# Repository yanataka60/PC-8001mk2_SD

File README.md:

# PC-8001mk2にSD-CARDからCMT形式ファイルのロード、セーブ機能

　PC-8001mk2でSD-CARDからCMT形式ファイルのロード、セーブ機能を実現するものです。

#### (2023.4.24追記)PC-8001mk2SRでは、Nモード、N80モードで動作しますが、N80SRモードでは動作しないとの報告がありました。

　CMTからの読み込み実行に数分掛かっていたゲームも数十秒で実行できます。

　PC-8001mk2_SD基板は、PC-8001mk2拡張スロットに挿入し、SDアクセスプログラムを書き込んだROMを本体内拡張ROMソケットに挿入して使います。

　なお、Arduino、ROMへ書き込むための機器が別途必要となります。

## 回路図
　KiCadフォルダ内のPC-8001mk2_SD.pdfを参照してください。

[回路図](https://github.com/yanataka60/PC-8001mk2_SD/blob/main/Kicad/PC-8001mk2_SD.pdf)

## 部品
|番号|品名|数量|備考|
| ------------ | ------------ | ------------ | ------------ |
||J2、J3のいずれか|||
|J2|Micro_SD_Card_Kit|1|秋月電子通商 AE-microSD-LLCNV (注1)|
|J3|MicroSD Card Adapter|1|Arduino等に使われる5V電源に対応したもの|
|U1|74LS04|1||
|U2|74LS30|1||
|U3|8255|1||
|U4|Arduino_Pro_Mini_5V|1|Atmega328版を使用 168版は不可。(注2)|
|C1|電解コンデンサ 16v100uF|1||
|C2-C4|積層セラミックコンデンサ 0.1uF|3||
||2764/28C64相当品|1|本体内拡張ROMソケットに挿入|
||ピンヘッダ|2Pin分|Arduino_Pro_MiniにはA4、A5用のピンヘッダが付いていないため別途調達が必要です 秋月電子通商 PH-1x40SGなど|
||ピンソケット(任意)|26Pin分|Arduino_Pro_Miniを取り外し可能としたい場合に調達します 秋月電子通商 FHU-1x42SGなど|

　　　注1)秋月電子通商　AE-microSD-LLCNVのJ1ジャンパはショートしてください。

　　　注2)Arduino Pro MiniはA4、A5ピンも使っています。

### MicroSD Card Adapterを使う(Rev1.1)
J3に取り付けます。

MicroSD Card Adapterについているピンヘッダを除去してハンダ付けするのが一番確実ですが、J3の穴にMicroSD Card Adapterをぴったりと押しつけ、裏から多めにハンダを流し込むことでハンダ付けをする方法もあります。なお、この方法の時にはしっかりハンダ付けが出来たかテスターで導通を確認しておいた方が安心です。

ハンダ付けに自信のない方はJ2の秋月電子通商　AE-microSD-LLCNVをお使いください。AE-microSD-LLCNVならパワーLED、アクセスLEDが付いています。

.JPG)

.JPG)

.JPG)

.JPG)

### MicroSD Card Adapterを使う(Rev1.0)
以下のピン番号を参考に変換基板等繋ぎ方は適宜対応してください。

|AE-microSD-LLCNVピン番号|MicroSD Card Adapterピン番号|信号名|
| ---------------------- | -------------------------- | ---- |
|1|2|5V|
|4|1|GND|
|5|5|SCK|
|6|3|MISO|
|7|4|MOSI|
|8|6|CS|

## ROMへの書込み
　Z80フォルダ内のEXT_ROM_SHIFT_OFF.bin、EXT_ROM_SHIFT_ON.bin、EXT_ROM_SHIFT_OFF.bin又はEXT_ROM_SHIFT_ON.binをROMライター(TL866II Plus等)を使って2764又は28C64に書き込み、本体内拡張ROMソケットに装着します。

　拡張ROMを本体内拡張ROMソケットに装着しますのでPC-8001mk2_SDを使いたくない時に拡張ROMを外すのは非常に面倒です。

　そこでSHIFTキー(又はAキー)を押しながら電源ON又はリセットすることでソフトウェア的に動作を切り替えられるようにしています。

　四つの違いは、以下のとおりです。

#### 2023.6.3追記
#### 従来SHIFTキーによりON、OFFを切り替えていましたが、CTRLキーを押しながら電源ON又はリセットで行うNモードとN80モードの切り替えとの併用に問題があるとの指摘がありました。
#### FDD等を使うことがなくON、OFFを切り替えることがほぼない方は従来のSHIFTキー方式で不都合は無いと思いますが、ON、OFFを切り替えることがある方はAキー方式をお使いください。

　●EXT_ROM_SHIFT_OFF.bin(通常PC-8001mk2_SDを使いたい人向け)

　　・普通に電源ON又はリセットする                -> PC-8001mk2_SDを使う。

　　・SHIFTキーを押しながら電源ON又はリセットする -> PC-8001mk2_SDを切り離す。

　●EXT_ROM_PRESS_A_OFF.bin(通常PC-8001mk2_SDを使いたい人向け)

　　・普通に電源ON又はリセットする                -> PC-8001mk2_SDを使う。

　　・Aキーを押しながら電源ON又はリセットする -> PC-8001mk2_SDを切り離す。

　●EXT_ROM_SHIFT_ON.bin(通常PC-8001mk2_SDを使わない人向け)

　　・普通に電源ON又はリセットする                -> PC-8001mk2_SDを切り離す。

　　・SHIFTキーを押しながら電源ON又はリセットする -> PC-8001mk2_SDを使う。

　●EXT_ROM_PRESS_A_ON.bin(通常PC-8001mk2_SDを使わない人向け)

　　・普通に電源ON又はリセットする                -> PC-8001mk2_SDを切り離す。

　　・Aキーを押しながら電源ON又はリセットする -> PC-8001mk2_SDを使う。

　ソースはPC-8001_SDリポジトリ、Z80フォルダ内のEXT_ROM.sに統合されています。

　アッセンブルするときは、53行をコメントアウトし、56行のセミコロン (;)を削除してください。

　また、四つを切り替えるためには126行から125行までを必要な行についてセミコロン (;)を削除し不必要な行にセミコロン (;)をつけてコメントアウトします。

#### 2023.7.9追記
#### FDDを繋いでいない時は問題ないのですが、FDDを繋ぐとEXT_ROM_SHIFT_OFF.bin、EXT_ROM_PRESS_A_OFF.binが正常に動作しない時があります。
#### Nモードでは正常に動作しますので問題ありません。
#### N80モードでN80 DISK BASICを起動したとき、「How many files?」と聞かれますが、この数字を入力し、RETURNを押した直後にSHIFTキー又は、Aキーのチェックが行われるため、数字を入力するためにSHIFTキー又は、Aキーを押さずにRETURNを押すとSDが有効なまま起動してしまう。
#### 対策としては、
#### 1.「How many files?」と聞かれてもSHIFTキー又は、Aキーを離さずにRETURNを押して起動させる。
#### 2.N80 DISK BASIC起動後に次の対策プログラムをSDからロード、実行する。
 「N80 DISK BASIC REPAIR」フォルダにあるN80 DISK BASIC REPAIR.cmtをSDにコピーしておいてください。

 N80モードでN80 DISK BASICを起動します。SHIFTキー又は、Aキーを押しながら起動する必要はありません。

 N80 Disk BASICが起動したらHow many filesに値を入力します。

 OKが表示されたら「files N80」で検索し、見つかった「N80 DISK BASIC REPAIR.cmt」をロード、実行します。

 これでDISK BASICが正常に利用できます。

 N80 DISK BASIC REPAIR.cmtプログラム

 　　10 POKE &HF139,&HFF

 　　20 POKE &HF13A,&HD6

 　　30 POKE &HF14B,&H4C

 　　40 POKE &HF14C,&HD7

 　　50 POKE &HF14E,&H2

 　　60 POKE &HF14F,&HDC

 　　70 POKE &HF142,&HE7

 　　80 POKE &HF143,&HD6

 　　90 NEW

#### 注)N80 DISK BASICに複数のバージョンが存在する場合にはジャンプ先が異なる場合があるかもしれません。正常に動作しない場合には、「How many files?」と聞かれてもSHIFTキー又は、Aキーを離さずにRETURNを押して起動させた後、上述アドレスのジャンプ先アドレスデータを確認してみてください。

### PC-8001mk2へ拡張ROMの取付
　本体を裏返して6か所のネジを外します。

　4か所のネジを外して拡張スロットボックスを外します。

　空きICソケットがあるのでPC-8001mk2_SD用拡張ROMを取り付けます。ICの向きは左下がPin1になります。向きを間違えたまま電源を入れるとROMが壊れますので注意してください。

　拡張スロットボックス、ケースを元に戻して終了です。

#### なお、拡張スロットボックスが上手くはまっていないままPC-8001mk2の電源を入れると暴走するそうです。きちんと嵌っているか確認してください。

### PC-8001mk2SRへ拡張ROMの取付
#### 注)PC-8001mk2SRでは、Nモード、N80モードではPC-8001mk2_SDが使えますが、N80SRモードでは使えません。
　本体を裏返して3か所のネジを外します。

　上カバーの後部を持ち上げます。

　上カバーを前にずらすとカバーのツメが外れます。

　空きICソケットがあるのでPC-8001mk2_SD用拡張ROMを取り付けます。ICの向きは左下がPin1になります。向きを間違えたまま電源を入れるとROMが壊れますので注意してください。

　カバーを戻してからPC-8001mk_SD基板を拡張スロットに挿しますが、この段階で挿しても大丈夫です。

　ケースを元に戻して終了です。

## Arduinoプログラム
　PC-8001_SDと全く同じものを使用しています。

　PC-8001_SDでソケットを使用して差込式にしているのであればそのままPC-8001mk2_SDに差して使えます。

　Arduino IDEを使ってPC-8001_SDリポジトリ、Arduinoフォルダ、PC-8001_SDフォルダ内PC-8001_SD.inoを書き込みます。

　SdFatライブラリを使用しているのでArduino IDEメニューのライブラリの管理からライブラリマネージャを立ち上げて「SdFat」をインストールしてください。

　「SdFat」で検索すれば見つかります。「SdFat」と「SdFat - Adafruit Fork」が見つかりますが「SdFat」のほうを使っています。

注)Arduinoを基板に直付けしている場合、Arduinoプログラムを書き込むときは、拡張スロットから取り出し、74LS04を外したうえで書き込んでください。

## 拡張スロットへの挿入
### そのまま挿入する場合
　横幅が短くスロットのガイドレールに届きませんので厚さ5mm程度のゴム足などをつけて挿入します。

　試作基板ではカードエッジ部分の幅が足りず、挿入の仕方によっては電源がショートしてしまうことが危険がありましたが、公開に当たって幅を修正しています。

.JPG)

### 補助板をつけスロットのガイドレールを利用する場合
　基板の左右に補助板を取り付ければスロットのガイドレールに沿って挿入することができるようになります。

#### 本体後ろから見て右側に取り付ける補助版のサイズ(画像右側)
　84mm(奥行)×65mm(幅)×1.6mm(厚さ)

#### 本体後ろから見て左側に取り付ける補助版のサイズ(画像左側)
　84mm(奥行)×55mm(幅)×1.6mm(厚さ)

画像では不用となった基板をカットしてセロテープで仮止めしています。

.JPG)
.JPG)

## SD-CARD
　仕様はPC-8001_SDと同じです。

　出来れば8GB以下のSDカードを用意してください。

　ArduinoのSdFatライブラリは、SD規格(最大2GB)、SDHC規格(2GB～32GB)に対応していますが、SDXC規格(32GB～2TB)には対応していません。

　また、SDHC規格のSDカードであっても32GB、16GBは相性により動作しないものがあるようです。

　FAT16又はFAT32が認識できます。NTFSは認識できません。

　ルートに置かれた拡張子が「.CMT」のCMT形式ファイルのみ認識できます。(CMT形式以外のファイル、フォルダも表示されますがLOAD実行の対象になりません)

　CMT形式であれば複数のCMTファイルを一つのファイルとしてまとめてあっても認識します。

　例)

　　BASIC+機械語　　　　　　　　　　　　　->　LOAD "DOSファイル名"[CR]、MON[CR]、L[CR]

　　機械語+機械語　　　　　　　　　　　　->　MON[CR]、 L DOSファイル名[CR]、L[CR]

　　オートラン機能ファイル+BASIC　　　　　->　MON[CR]、L DOSファイル名[CR]（以下オートラン）

　　オートラン機能ファイル+BASIC+機械語　->　MON[CR]、L DOSファイル名[CR]（以下オートラン）

　　オートラン機能ファイル+機械語+機械語　->　MON[CR]、L DOSファイル名[CR]（以下オートラン）

　　など

　ファイル名は「.CMT」を含めて31文字まで、ただし半角カタカナ、及び一部の記号はArduinoが認識しないので使えません。パソコンでファイル名を付けるときはアルファベット、数字および空白でファイル名をつけてください。

## 使い方
　仕様はPC-8001_SDと同じです。

　PC-8001mk2_SD使用の有無はSHIFTキーを押しながら電源ON又はRESET又はAキーを押しながら電源ON又はRESETすることで切り替えてください。

### BASICコマンド
#### FILES[CR]又はFILES "文字列"[CR]
FILES[CR]とするとSD-CARDルートディレクトリにあるファイルの一覧を表示します。

FILES "文字列"[CR]とするとSD-CARDルートディレクトリにあるその文字列から始まるファイルの一覧を表示します。

20件表示したところで指示待ちになるので打ち切るならESC又は↑を入力すると打ち切られ、Bキーで前の16件に戻ります。それ以外のキーで次の16件を表示します。

　行頭に「LOAD "」を付加して表示してあるので実行したいファイルにカーソルキーを合わせて[CR]キーを押すだけでLOAD可能です。

　表示される順番は、登録順となりファイル名アルファベッド順などのソートした順で表示することはできません。

##### 参考
　FILES "文字列"[CR]とする場合、基本的にはダブルコーテーションが無くても機能しますが、数字で始まるファイル名の場合ダブルコーテーションが無いと検索できません。

　× FILES 3

　○ FILES "3"

#### LOAD "DOSファイル名"[CR]
指定したDOSフィル名のBASICプログラムをSD-CARDからLOADします。

ファイル名の前に"(ダブルコーテーション)は必須ですが、ファイル名の後ろに"(ダブルコーテーション)は有っても無くても構いません。

ファイル名の最後の「.CMT」も有っても無くても構いません。

　例)

　　LOAD "TEST" -> DOSファイル名「TEST.CMT」を読み込みます。

　　LOAD "TEST.BAS" -> DOSファイル名「TEST.BAS.CMT」を読み込みます。

　　LOAD "TEST.BAS.CMT" -> DOSファイル名「TEST.BAS.CMT」を読み込みます。

##### 参考
　基本的にはDOSファイル名をダブルコーテーションで括らなくても機能しますが、数字で始まるファイル名の場合ダブルコーテーションが無いとLOADできません。

　NOT FIND FILEと表示されます。

　× LOAD 3D MAZE

　○ LOAD "3D MAZE"

#### LOAD ""[CR]（※多段ロードファイルの２段目以降のみ有効）
直前に読み込まれたDOSファイルが多段ロード用に複数のCMTファイルが連結されており、２段目以降がBASICプログラムであった時のみ有効に動作し、BASICプログラムをSD-CARDからLOADします。

#### SAVE "DOSファイル名"[CR]
BASICプログラムを指定したDOSフィル名でSD-CARDに上書きSAVEします。

ファイル名の省略は出来ません。

ファイル名の前に"(ダブルコーテーション)は必須ですが、ファイル名の後ろに"(ダブルコーテーション)は有っても無くても構いません。

ファイル名の最後の「.CMT」も有っても無くても構いません。

指定したDOSファイル名の最初の６文字がCMT形式の中に保存されるファイル名として使われます。

BASICプログラムであることを識別するために「.BAS」を付けることを推奨します。

　例)

　　SAVE "TEST" -> 「TEST.CMT」で保存される。

　　SAVE "TEST.BAS" -> 「TEST.BAS.CMT」で保存される。

##### 参考
　基本的にはDOSファイル名をダブルコーテーションで括らなくても機能しますが、数字で始まるファイル名の場合ダブルコーテーションが無いとSAVEできません。

　SD-CARD INITIALIZE ERRORと表示されます。

#### KILL DOSファイル名[CR]
指定したDOSフィル名がSD-CARDに存在すればSD-CARDから削除します。

ファイル名の最後に「.CMT」も指定してもしなくても構いません。

##### 参考
　基本的にはDOSファイル名をダブルコーテーションで括らなくても機能しますが、数字で始まるファイル名の場合ダブルコーテーションが無いとKILLできません。

　NOT FIND FILEと表示されます。

　× KILL 3D MAZE

　○ KILL "3D MAZE"

### MONITORコマンド
#### F[CR]又はF 文字列[CR]
文字列を入力せずにF[CR]のみ入力するとSD-CARDルートディレクトリにあるファイルの一覧を表示します。

文字列を付けて入力すればSD-CARDルートディレクトリにあるその文字列から始まるファイルの一覧を表示します。

20件表示したところで指示待ちになるので打ち切るならESC又は↑を入力すると打ち切られ、Bキーで前の16件に戻ります。それ以外のキーで次の16件を表示します。

　行頭に「*L 」を付加して表示してあるので実行したいファイルにカーソルキーを合わせて[CR]キーを押すだけでLOAD可能です。

　表示される順番は、登録順となりファイル名アルファベッド順などのソートした順で表示することはできません。

##### 例)
　　F[CR]

　　F S[CR]

　　F SP[CR]

#### L DOSファイル名[CR]
指定したDOSフィル名の機械語プログラムをSD-CARDからLOADします。

ファイル名の最後の「.CMT」は有っても無くても構いません。

　例)

　　L TEST -> DOSファイル名「TEST.CMT」を読み込みます。

　　L TEST.BIN -> DOSファイル名「TEST.BIN.CMT」を読み込みます。

　　L TEST.BIN.CMT -> DOSファイル名「TEST.BIN.CMT」を読み込みます。

#### L[CR]（※多段ロードファイルの２段目以降のみ有効）
直前に読み込まれたDOSファイルが多段ロード用に複数のCMTファイルが連結されており、２段目以降が機械語プログラムであった時のみ有効に動作し、機械語プログラムをSD-CARDからLOADします。

#### W 16進数4桁 16進数4桁 DOSファイル名[CR]
1番目の16進数4桁が表すアドレスから2番目の16進数4桁が表すアドレスまでを指定したDOSファイル名でSD-CARDに機械語として上書き保存します。

ファイル名の最後に「.CMT」を指定してもしなくても構いません。

またWの後ろや各パラメータ間に空白が有っても無くても構いません。

機械語プログラムであることを識別するために「.BIN」等を付けることを推奨します。

　例)

　　W 0000 001F TEST -> 　　0000番地から001F番地までをDOSファイル名「TEST.CMT」で保存する。

　　W 0000 001F TEST.BIN -> 0000番地から001F番地までをDOSファイル名「TEST.BIN.CMT」で保存する。

#### G 16進数4桁[CR]
16進数4桁が表すアドレスにジャンプします。

Gの後ろに空白があっても無くても構いません。

#### B[CR]
BASICに復帰します。MONITORでのコマンド入力をスクリーンエディタにしたため、CTRL+Bが機能しないので代替コマンドです。

CTRL+Cと動作は同じです。

#### CTRL+C
BASICに復帰します。MONITORでのコマンド入力をスクリーンエディタにしたため、CTRL+Bが機能しないので代替コマンドです。

B[CR]と動作は同じです。

#### S 16進数4桁 {16進数2桁}の繰り返し[CR]
PC-8001のメモリに16進数4桁が表すアドレスから16進数2桁が表すデータを書き込みます。

[CR]で改行すると有効な16進数2桁データを書き込んだ後、次に書き込みとなるアドレスを表示しますので続きの16進数2桁のデータを入力して[CR]で改行します。

アドレス表示の次に16進数2桁のデータを入力せずに[CR]を押すと終了します。

Sの後ろ、アドレス、データの区切りに空白が有っても無くても構いません。

例)

以下の例はすべて同じ結果となります。

　SA0001122334455

　SA000 11 22 33 44 55

　S A000 1122334455

　S A0001122334455

　S A000 1122 3344 55

#### D 16進数4桁[CR]
16進数4桁が表すアドレスからPC-8001のメモリの内容を128Byteを一画面として表示します。

一画面表示したところで「NEXT:ANY BACK:B BREAK:ESC」と表示して指示待ちとなるのでBで前の128Byteを表示、ESCで中止、それ以外のキーで次の128Byteの表示となります。

一画面表示している途中でもESCでいつでも中止できます。

### ファンクションキーを利用したオートラン機能
ファンクションキーを利用したオートラン機能に対応していますが、一部オリジナルと異なる点があります。

そこでオートラン機能ファイルをロードする時にPC-8001mk2_SDの仕様に自動変換する機能を付けました。(2022.8.21実装)

以下の修正点についてオートラン機能ファイルをロードする時に自動的に修正ロードされますのでオートラン機能ファイルを修正する必要はありません。当然、修正してあっても機能します。

自動で修正される点

　1　CTRL+BではMONITORからBASICへ復帰できません。CTRL+Cに修正されます。

　2　SD-CARDからのBASICプログラムをLOADするコマンドは「LOAD」で、1本のCMTファイルとなっていればファイル名を指定する必要もありませんので「CLOAD"ファイル名"」は「LOAD""」に修正されます。

## 操作上の注意
　~~「SD-CARD INITIALIZE ERROR」と表示されたときは、SD-CARDをいったん抜き再挿入したうえでArduinoをリセットしてください。~~

　~~SD-CARDにアクセスしていない時に電源が入ったままで SD-CARDを抜いた後、再挿入しSD-CARDにアクセスすると「SD-CARD INITIALIZE ERROR」となる場合があります。再挿入した場合にはSD-CARDにアクセスする前にArduinoを必ずリセットしてください。~~

　~~SD-CARDの抜き差しは電源を切った状態で行うほうがより確実です。~~

　(2024.3.10) SD-CARDにアクセスしていない時に電源が入ったままでSD-CARDを抜くと再度SD-CARDを挿入してもSD-CARDにアクセスできない問題を解消しました。(Arduinoを最新版に書き換えてください)

　再度SD-CARDを挿入した後、FILES、LOAD、SAVE等でSD-CARDに3回ほどアクセスすれば復旧します。

## New CITY HEROをSDから読み込み実行するための修正
　PC-8001mk2_SDを使うことで内藤 時浩さんが頒布されているNew CITY HEROをPC-8001mk2実機で手軽に遊べるようになりますが、New CITY HEROは機械語の多段ロード方式で２段目のプログラム内にCMTからの読み込みルーチンをコールしている箇所がありますので、そこをSDから読み込むためのコール先に修正する必要があります。

　修正箇所、修正内容はPC-8001_SD用の修正と全く同じですのでPC-8001_SD用にNew CITY HEROを修正してあればそのまま実行することができます。

### 修正手順
　New CITY HEROのCMT形式ファイルに次の手順で修正を行いPC-8001mk2_SD用のCMT形式ファイルを作り、SD-CARDに保存してください。

#### 2023.6.10 DumpListEditorのPatch File機能で作る方法に修正しました。

~~1　頒布していただいたNew City HeroのCMTファイルをbugfire2009さんの「DumpListEditor」にDrag&Dropする~~

~~2　表示される3つのBINファイルをうち、2番目のBINファイルを「マシン語入力に送る」を押す~~

~~3 「CD F3 0B」を検索して「00 00 00」に修正(1箇所)~~

~~4 「9E 5F」を検索して「06 60」に修正(14箇所)~~

~~5　v1.1.1の場合、「9E 5F」の検索では13箇所しか見つからないので「CD 9E」で検索し、「9E」を「06」に次行最初の「5F」を「60」に修正(1箇所)~~

~~6　修正が終わったら「ファイル整理画面にPaste」を押す~~

~~7　ファイル整理画面に戻ったことを確認し、「cmt書出し」を押してPC-8001_SD対応済cmtファイルとして保存する~~

　1　頒布していただいたNew City HeroのCMTファイルをbugfire2009さんの「DumpListEditor」にDrag&Dropする

　2　「BASIC入力」タブをクリックして言語「Patch File」を選択する。

　3　表示されているPathc File Sampleをすべて削除し、次の15行に入れ替える。

/CD,F3,0B/=00,00,00

/CD,9E,5F/=CD,06,60

/CD,9E,5F/=CD,06,60

/CD,9E,5F/=CD,06,60

/CD,9E,5F/=CD,06,60

/CD,9E,5F/=CD,06,60

/CD,9E,5F/=CD,06,60

/CD,9E,5F/=CD,06,60

/CD,9E,5F/=CD,06,60

/CD,9E,5F/=CD,06,60

/CD,9E,5F/=CD,06,60

/CD,9E,5F/=CD,06,60

/CD,9E,5F/=CD,06,60

/CD,9E,5F/=CD,06,60

/CD,9E,5F/=CD,06,60

　4　「ファイル整理画面にPaste」を押す。

　5　ファイル整理画面に「PATCH.patch」というファイルが追加される。ファイルの位置はどこにあっても可。

　6　「cmt書出し」を押してPC-8001_SD対応済cmtファイルとして保存する。

## DumpListEditor動画作成機で作られたCMTファイルへの対応

　DumpListEditor動画作成機で作られたCMTファイルのうち、「Chain(cmt出力時のみ)」をチェックして作られたプログラムはCMTルーチンをコールしますので修正が必要となります。

セミグラ作成機＆動画作成機

https://bugfire2009.ojaru.jp/semigra/

で紹介されているきらびぃさん作成の

「メガCD版シルフィードのデモをPC8001で再生してみたフル版(修正版)」

「PC8001でBad Apple全編をcmt化」

の二つがこの機能を使っていますのでPC-8001mk2_SDで再生するにはパッチ当てが必要になりますが、N80モードでは「メガCD版シルフィードのデモをPC8001で再生してみたフル版(修正版)」は途中で止まってしまいます。Nモードでは最後まで再生出来たので「Chain(cmt出力時のみ)」をチェックして作られたファイルのPC-8001mk2_SDでの再生は現時点でNモードでのみ可能と考えてください。(CMTであればN80モードでも再生出来てます。)

　この二つのファイルの具体的な修正方法は、PC-8001_SDのREADME.mdを参照してください。

## SDアクセスサービスルーチン
　「プログラム側からファイル名を指定してSDから読み込む」機能と「プログラム側からファイル名を指定してSDへ書き込む」機能を追加しました。

#### 　この機能を活用するには、この機能に対応したアプリケーションプログラムが必要となります。

　以下にサービスルーチンの仕様とエントリポイントを公開します。

|エントリポイント|名前|用途|
| -------------- | -- | -- |
|600F|ROPEN|READ FILE OPEN|

　HL <- DOS_FILENAME先頭アドレス

　HLレジスタが示すDOS_FILENAMEで読み込み用ファイルをオープン

　DOS_FILENAMEは31文字まで、最後に00Hをつけること。

　フラグレジスタ以外のレジスタは変化しない。

　正常終了 CF=0、異常終了 CF=1

|エントリポイント|名前|用途|
| -------------- | -- | -- |
|6006|D_5F9E|5F9EH代替|

　読み出されたデータ -> A

　読み込み用としてOPENしているファイルから1BYTE読み出し

|エントリポイント|名前|用途|
| -------------- | -- | -- |
|6009|H_5F3A|5F3AH代替|

　読み出しオープンされているファイルから機械語フォーマットで保存されている機械語を読み出す。

　WORK AREA:FF3D～FF3E メモリ書き込み開始アドレス

　正常終了 CF=0、異常終了 CF=1

|エントリポイント|名前|用途|
| -------------- | -- | -- |
|600C|MONHOT|5C66H代替|

　Gコマンドで実行する機械語プログラムからモニタに戻るときには、ここへのジャンプを指定。

　オートラン機能が実行中であれば継続して実行される。

|エントリポイント|名前|用途|
| -------------- | -- | -- |
|6012|WAOPEN|WRITE FILE APPEND OPEN|

　HL <- DOS_FILENAME先頭アドレス

　HLレジスタが示すDOS_FILENAMEで追加書き込み用としてファイルをオープン

　DOS_FILENAMEは31文字まで、最後に00Hをつけること。

　フラグレジスタ以外のレジスタは変化しない。

　正常終了 CF=0、異常終了 CF=1

|エントリポイント|名前|用途|
| -------------- | -- | -- |
|601B|WNOPEN|WRITE FILE NEW OPEN|

　HL <- DOS_FILENAME先頭アドレス

　HLレジスタが示すDOS_FILENAMEで書き込み用として新たにファイルをオープン。同名のDOS_FILENAMEのファイルがある場合は削除したのちにオープンする。

　DOS_FILENAMEは31文字まで、最後に00Hをつけること。

　フラグレジスタ以外のレジスタは変化しない。

　正常終了 CF=0、異常終了 CF=1

|エントリポイント|名前|用途|
| -------------- | -- | -- |
|6018|D_5F2F|5F2FH代替|

　A <- 書き込みデータ

　書込み用でオープンされているファイルにAレジスタのデータを追加書込みする。

　フラグレジスタ以外のレジスタは変化しない。

　正常終了 CF=0、異常終了 CF=1

|エントリポイント|名前|用途|
| -------------- | -- | -- |
|6015|D_5ED9|5ED9H代替|

　HL <- 書き込み開始アドレス

　DE <- 書き込み終了アドレス

　書込み用でオープンされているファイルに書き込み開始アドレスから書き込み終了アドレスまでのメモリ内容を機械語フォーマットで書出し、クローズする。

　WORK AREA:FF3D～FF3E 書き込み開始アドレス

　　　　　　　FF3F～FF40 書き込み終了アドレス

　正常終了 CF=0、異常終了 CF=1

|エントリポイント|名前|用途|
| -------------- | -- | -- |
|601E|WCLOSE|WRITE FILE CLOSE|

　書込み用ファイルをクローズする。

　フラグレジスタ以外のレジスタは変化しない。

　正常終了 CF=0、異常終了 CF=1

### SDアクセスサービスルーチンのテスト用プログラム
　SDアクセスサービスルーチンのテストと使い方のサンプルとしてPC-8001_SDリポジトリ、Z80フォルダ内SD Access service routine Testフォルダにテストプログラムを置きました。

　「sd_test.BIN.CMT」と「SD_TEST2.BIN.CMT」の二つをSDカードにコピーしてモニタ Lコマンドで「sd_test.BIN.CMT」を読み込み実行してください。

　画面に01からFFまで表示した後、「SD TEST OK」と表示して終了します。

　SDカードには「SD_WRITE_READ_TEST.DAT」と「SD_WRT_DIRECT_TEST.BIN.CMT」の二つのファイルが出来上がっているはずです。

　「SD_WRITE_READ_TEST.DAT」は510Byteのファイルサイズで01からFF、FFから01までのデータが格納されているはずです。

　「SD_WRT_DIRECT_TEST.BIN.CMT」は161ByteのファイルサイズでA000h～A096hまでのメモリ内容を機械語フォーマットのcmtとして保存した内容となっているはずです。

## 謝辞
　基板の作成に当たり以下のデータを使わせていただきました。ありがとうございました。

　Arduino Pro Mini

　　https://github.com/g200kg/kicad-lib-arduino

　AE-microSD-LLCNV

　　https://github.com/kuninet/PC-8001-SD-8kRAM

　New CITY HEROの修正点を公開することを快く承諾してくださった内藤 時浩様、ありがとうございました。

　NBASICのコマンド追加に当たっては、ちくらっぺ様のSD-DOSがとても参考になりました。ありがとうございました。

　　https://github.com/chiqlappe/SD-DOS

　PC-8001mk2SRでの動作確認をなつさんに行っていただきました。ありがとうございました。

　スタック領域を破壊し正常にロードが出来ない機械語プログラムの事例について情報を提供してくださった久保ちゃん様、ありがとうございました。

　SHIFTキーによるON、OFFの切り替えは、CTRLキーを押しながら電源ON又はリセットで行うNモードとN80モードの切り替えとの併用に問題があると指摘していただいた内藤 時浩@NAITOTokihiro様、ありがとうございました。

## 追記
2022.8.18

　DumpListEditorの動画作成機機能で作成されたcmtファイルについて追記しました。

2022.8.21

　MONITOR Lコマンドで読み込み時にオートラン機能ファイルであればCTRL+B、CLOADをSD用に書き換えるようにした

2022.9.25

　MicroSD Card Adapter用の端子を付加し、基板をRev1.1に更新。

2022.11.7

　部品リストに2764が落ちていたので追加。

2023.4.24

　PC-8001mk2SRでの動作状況を追記しました。

2023.5.30

　E800h以降までロードする機械語プログラムをロードするとスタック領域を破壊してしまうことに対処。

2023.6.3

　SD機能のON、OFFにAキー方式を追加。

2023.6.10

　SDアクセスサービスルーチンを追加、エントリポイントを公開。5F3AH代替ルーチンを見直し。

2023.6.25

　拡張ROMの取付方法を追記しました。

2023.7.9

　N80モードでN80 DISK BASICを使うときの対策を追加しました。

2023.9.11

　PC-8001 N-BASIC V1.0の場合、MONITORに入ることでPC-8001_SDの初期化が行われるように拡張ROM用ソースコードを修正したため、今後アセンブルし直したときに該当コードが含まれるようになりますが、N-BASIC 1.0の時のみ有効になるのでPC-8001mk2_SDに影響はありません。

2023.10.5

　ファイル名長さの仕様を訂正

　　誤)「.CMT」を除いて32文字      正)「.CMT」を含めて31文字

2024.1.15

　SDカードは8GB以下が望ましいことを追記。

2024.3.12

　電源が入ったままでSD-CARDを抜くと再度SD-CARDを挿入してもSD-CARDにアクセスできない問題を解消した。

2024.9.6

　最新のEXT-ROMであるにも関わらず内藤様のXeGraderで「SD drive of newer detected.」と判定できないバクを修正

2024.9.11

　サービスルーチンでの使用ワークエリアを追記

2025.8.30

　サービスルーチンで解説していなかった600Ch(MONHOT)の解説を追加。

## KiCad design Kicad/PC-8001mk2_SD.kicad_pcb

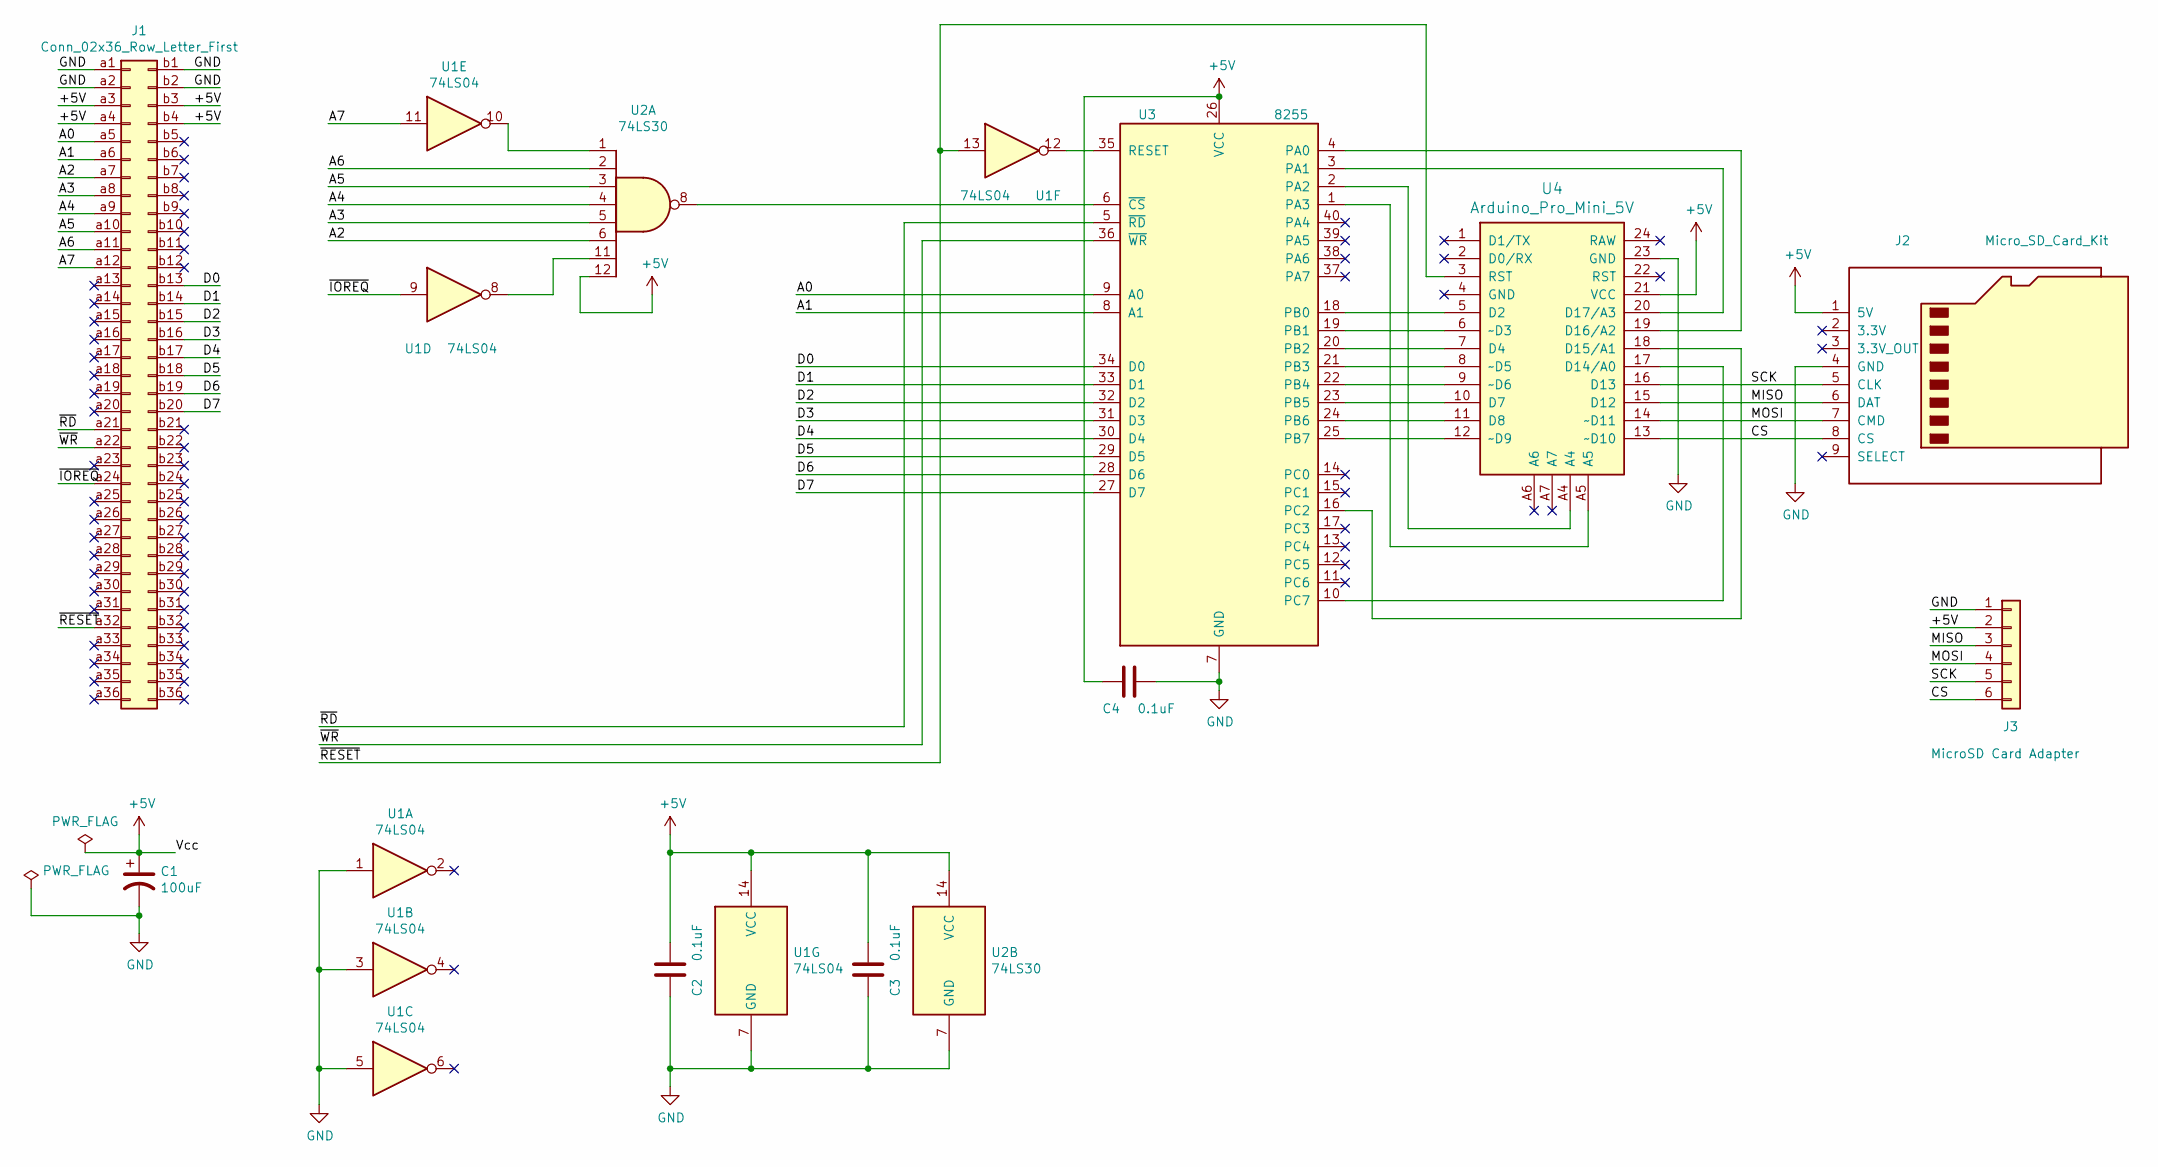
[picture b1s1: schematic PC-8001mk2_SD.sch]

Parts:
C1: 100uF; CP_Radial_D5.0mm_P2.50mm
C2, C3, C4: 0.1uF; C_Rect_L4.0mm_W2.5mm_P2.50mm
J1: Conn_02x36_Row_Letter_First; BUS_PC8001MK2
J2: Micro_SD_Card_Kit; AE-microSD-LLCNV
J3: MicroSD Card Adapter; PinSocket_1x06_P2.54mm_Vertical
U1: 74LS04; DIP-14_W7.62mm_LongPads
U2: 74LS30; DIP-14_W7.62mm_LongPads
U3: 8255; DIP-40_W15.24mm_LongPads
U4: Arduino_Pro_Mini_5V; Arduino_Pro_Mini

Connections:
+5V: C1.1, C2.2, C3.2, C4.1, J1.a3, J1.a4, J1.b3, J1.b4, J2.1 (5V), J3.2, U1.14 (VCC), U2.12, U2.14 (VCC), U3.26 (VCC), U4.21 (VCC)
/A0: J1.a5, U3.9 (A0)
/A1: J1.a6, U3.8 (A1)
/A2: J1.a7, U2.6
/A3: J1.a8, U2.5
/A4: J1.a9, U2.4
/A5: J1.a10, U2.3
/A6: J1.a11, U2.2
/A7: J1.a12, U1.11
/CS: J2.8 (CS), J3.6, U4.13 (~~D10)
/D0: J1.b13, U3.34 (D0)
/D1: J1.b14, U3.33 (D1)
/D2: J1.b15, U3.32 (D2)
/D3: J1.b16, U3.31 (D3)
/D4: J1.b17, U3.30 (D4)
/D5: J1.b18, U3.29 (D5)
/D6: J1.b19, U3.28 (D6)
/D7: J1.b20, U3.27 (D7)
/MISO: J2.6 (DAT), J3.3, U4.15 (D12)
/MOSI: J2.7 (CMD), J3.4, U4.14 (~~D11)
/SCK: J2.5 (CLK), J3.5, U4.16 (D13)
/~IOREQ: J1.a24, U1.9
/~RD: J1.a21, U3.5 (~RD~)
/~RESET: J1.a32, U1.13, U4.3 (RST)
/~WR: J1.a22, U3.36 (~WR~)
GND: C1.2, C2.1, C3.1, C4.2, J1.a1, J1.a2, J1.b1, J1.b2, J2.4 (GND), J3.1, U1.1, U1.3, U1.5, U1.7 (GND), U2.7 (GND), U3.7 (GND), U4.23 (GND)
unnamed: U1.8, U2.11
unnamed: U1.10, U2.1
unnamed: U1.12, U3.35 (RESET)
unnamed: U2.8, U3.6 (~CS~)
unnamed: U3.1 (PA3), U4.A5
unnamed: U3.2 (PA2), U4.A4
unnamed: U3.3 (PA1), U4.20 (D17/A3)
unnamed: U3.4 (PA0), U4.19 (D16/A2)
unnamed: U3.10 (PC7), U4.17 (D14/A0)
unnamed: U3.16 (PC2), U4.18 (D15/A1)
unnamed: U3.18 (PB0), U4.5 (D2)
unnamed: U3.19 (PB1), U4.6 (~~D3)
unnamed: U3.20 (PB2), U4.7 (D4)
unnamed: U3.21 (PB3), U4.8 (~~D5)
unnamed: U3.22 (PB4), U4.9 (~~D6)
unnamed: U3.23 (PB5), U4.10 (D7)
unnamed: U3.24 (PB6), U4.11 (D8)
unnamed: U3.25 (PB7), U4.12 (~~D9)

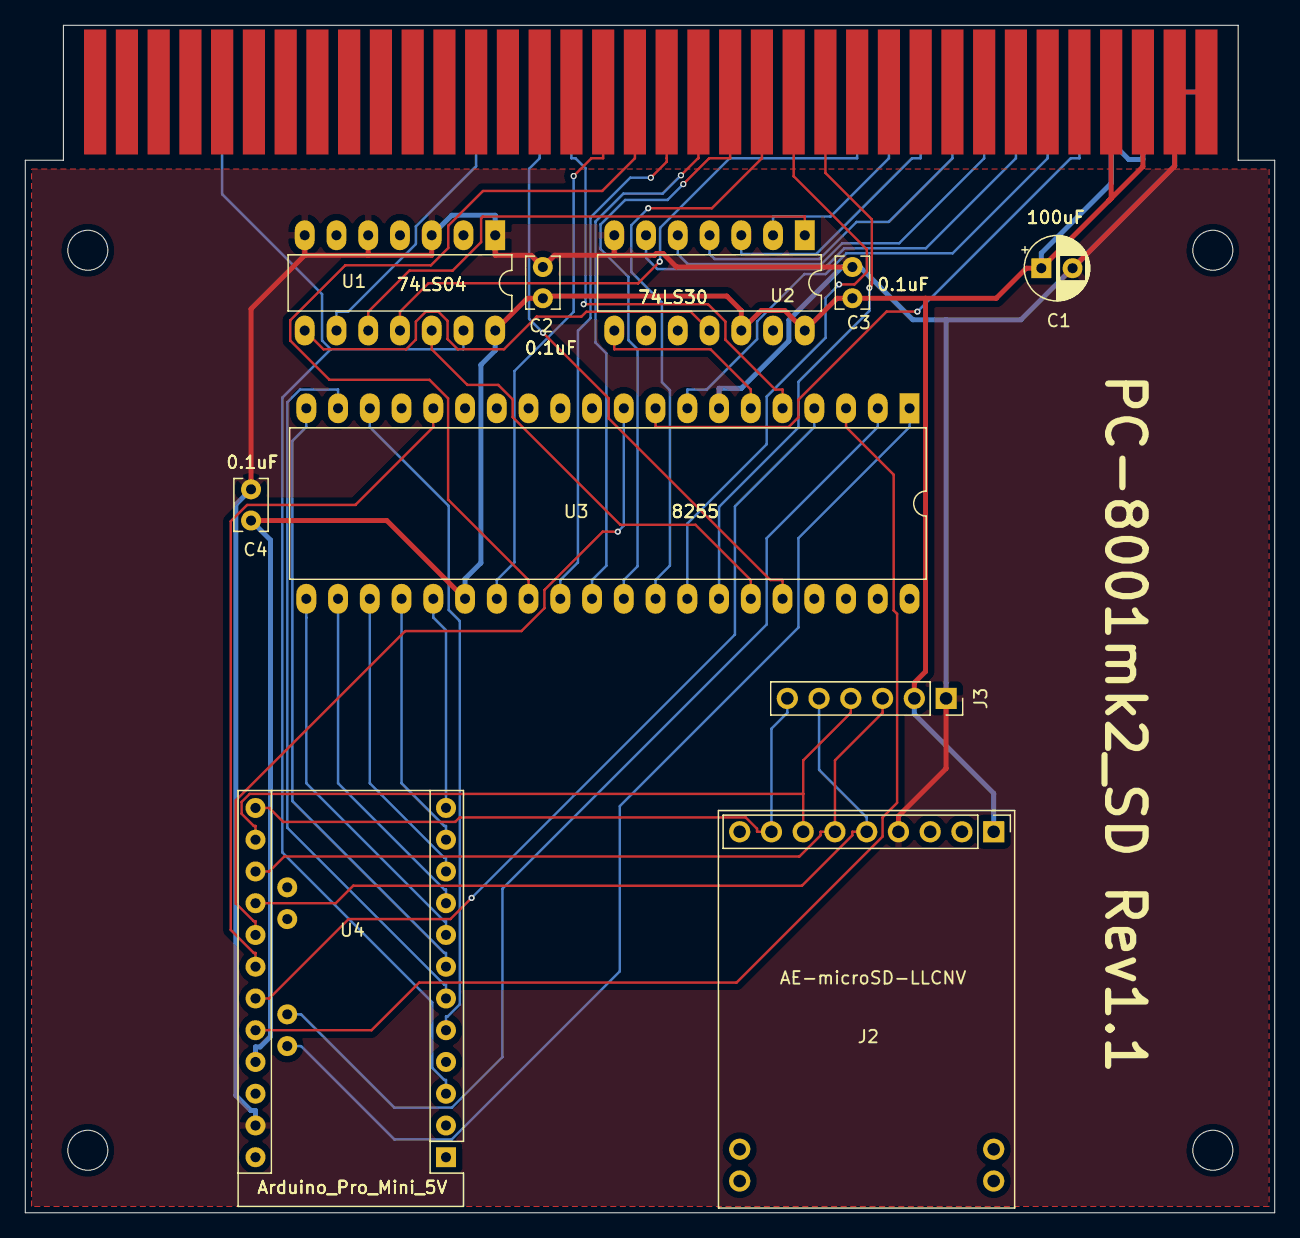
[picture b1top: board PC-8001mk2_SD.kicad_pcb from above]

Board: 2 copper layers, 99.9 x 95.0 mm, 15 parts (1 on the bottom side), 44 nets.

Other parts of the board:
MH1, MH2, MH3, MH4: MountingHole_3.2mm_M3
